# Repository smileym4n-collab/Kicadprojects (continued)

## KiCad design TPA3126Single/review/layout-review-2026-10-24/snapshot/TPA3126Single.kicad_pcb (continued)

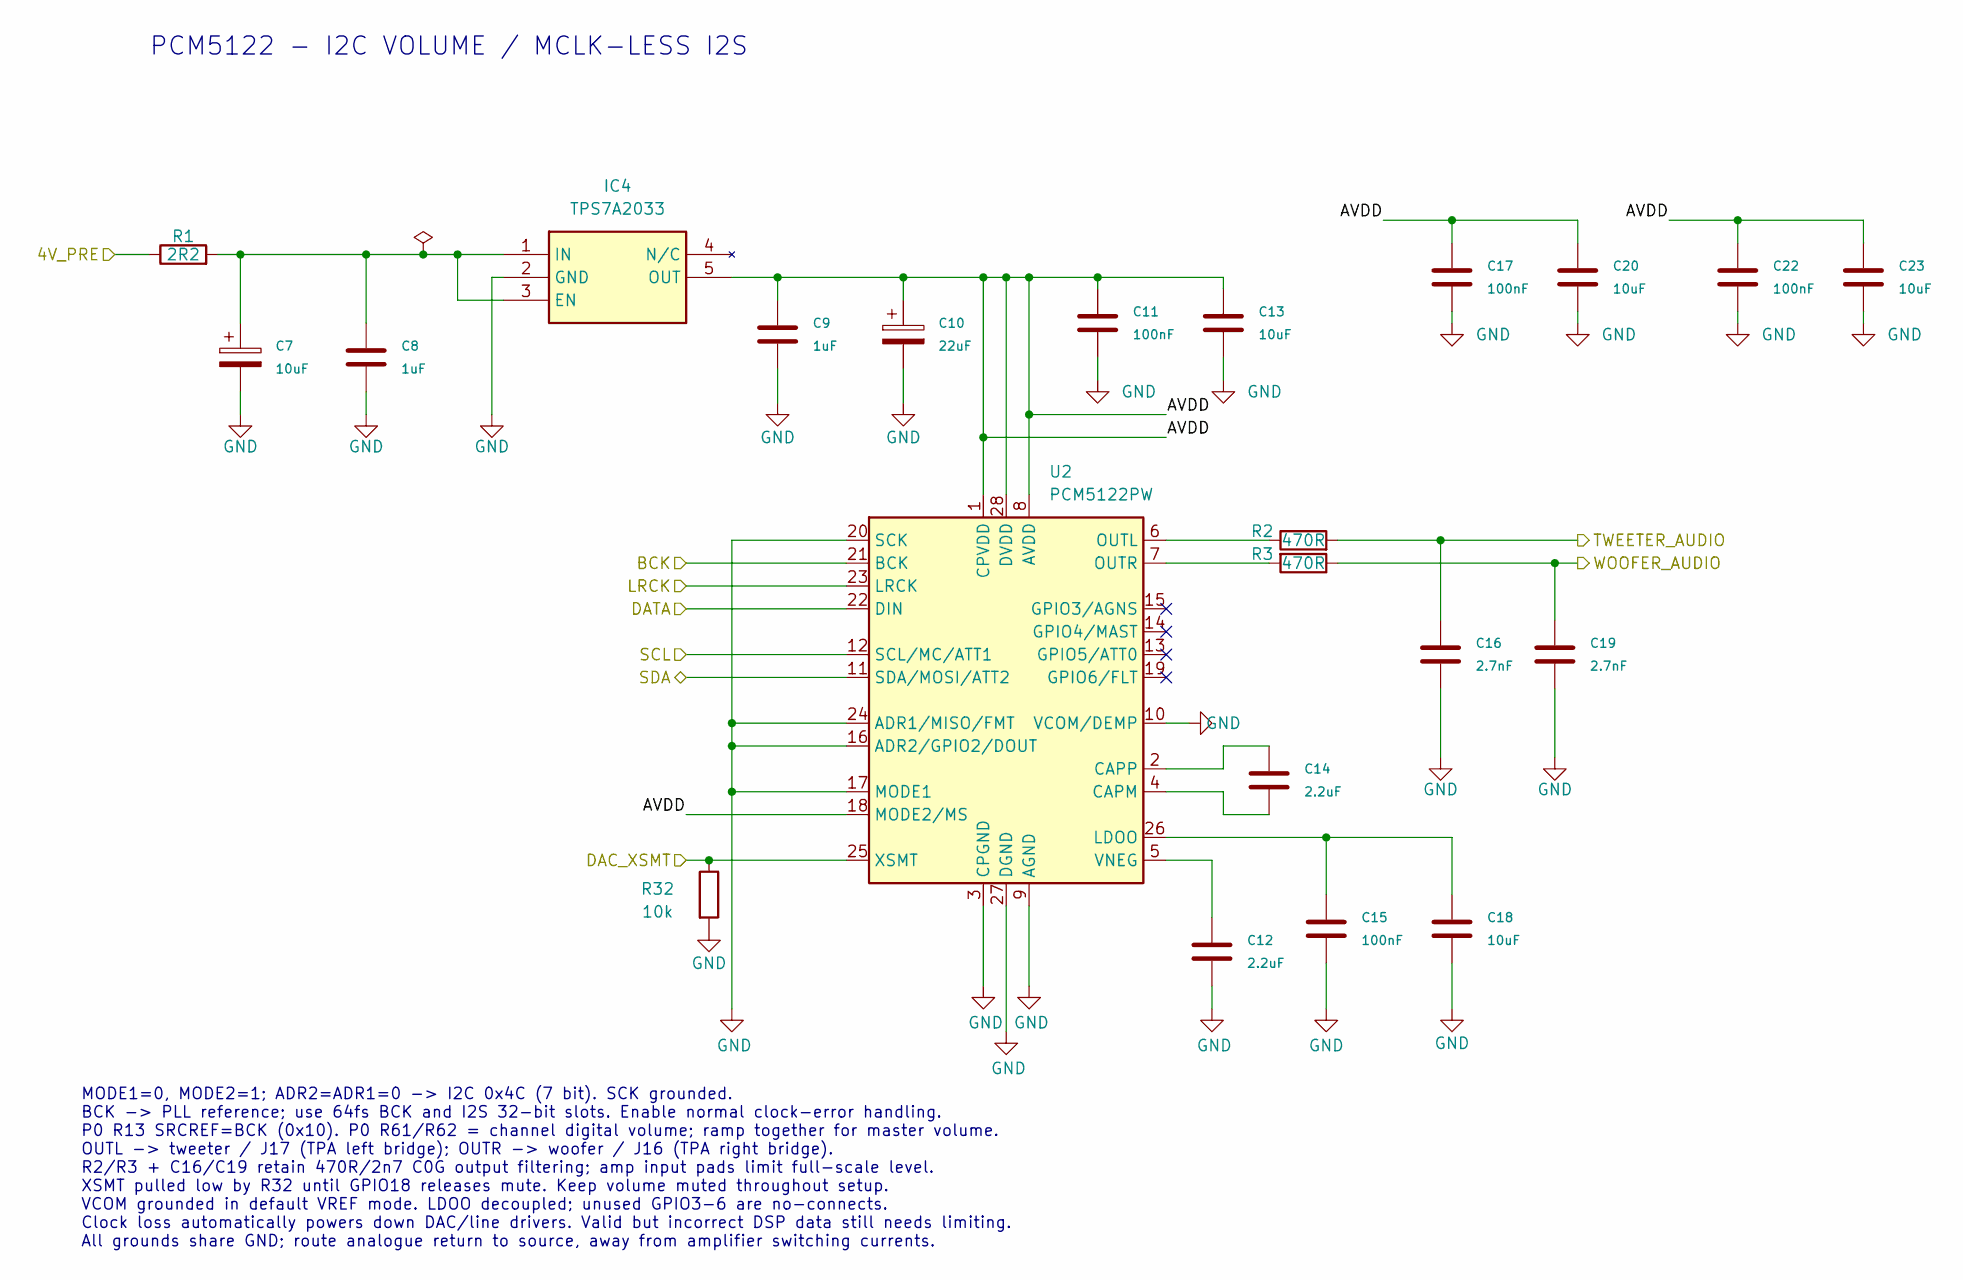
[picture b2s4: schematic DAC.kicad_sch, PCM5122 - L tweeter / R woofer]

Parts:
C7: 10uF; CP_Radial_D5.0mm_P2.00mm; MPN UFW1H100MDD
C8, C9: 1uF; C_1206_3216Metric_Pad1.33x1.80mm_HandSolder; MPN CL31B105KBHNFNE
C10: 22uF; CP_Radial_D5.0mm_P2.00mm; MPN UFW1E220MDD
C11, C15, C17, C22: 100nF; C_1206_3216Metric_Pad1.33x1.80mm_HandSolder; MPN C1206C104K5RACTU
C12, C14: 2.2uF; C_0805_2012Metric_Pad1.18x1.45mm_HandSolder; MPN CL21B225KPFNNNE
C13, C20, C23: 10uF; C_0805_2012Metric_Pad1.18x1.45mm_HandSolder; MPN CL21A106KOQNNNF
C16, C19: 2.7nF; C_0805_2012Metric_Pad1.18x1.45mm_HandSolder; MPN 0805N272J500CT
C18: 10uF; C_1206_3216Metric_Pad1.33x1.80mm_HandSolder; MPN TMK316B7106KL-TD
IC4: TPS7A2033; SOT95P280X145-5N; Mouser Part Number 595-TPS7A2033PDBVR
R1: 2R2; R_0805_2012Metric_Pad1.20x1.40mm_HandSolder
R2, R3: 470R; R_0805_2012Metric_Pad1.20x1.40mm_HandSolder
R32: 10k; R_0603_1608Metric_Pad0.98x0.95mm_HandSolder; Manufacturer_Part_Number RC0603FR-0710KL
U2: PCM5122PW; TSSOP-28_4.4x9.7mm_P0.65mm; MPN PCM5122PWR

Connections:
/4V_PRE: R1.1; also elsewhere on the board
/AMP/TWEETER_AUDIO: C16.1, R2.2; also elsewhere on the board
/AMP/WOOFER_AUDIO: C19.1, R3.1; also elsewhere on the board
/DAC/AVDD: C9.1, C10.1, C11.1, C13.1, C17.1, C20.1, C22.1, C23.1, IC4.5 (OUT), U2.1 (CPVDD), U2.8 (AVDD), U2.18 (MODE2/MS), U2.28 (DVDD)
/DAC/BCK: U2.21 (BCK); also elsewhere on the board
/DAC/DAC_XSMT: R32.1, U2.25 (XSMT); also elsewhere on the board
/DAC/DATA: U2.22 (DIN); also elsewhere on the board
/DAC/LRCK: U2.23 (LRCK); also elsewhere on the board
/ESP32/SCL: U2.12 (SCL/MC/ATT1); also elsewhere on the board
/ESP32/SDA: U2.11 (SDA/MOSI/ATT2); also elsewhere on the board
GND: C7.2, C8.2, C9.2, C10.2, C11.2, C12.2, C13.2, C15.2, C16.2, C17.2, C18.2, C19.2, C20.2, C22.2, C23.2, IC4.2 (GND), R32.2, U2.3 (CPGND), U2.9 (AGND), U2.10 (VCOM/DEMP), U2.16 (ADR2/GPIO2/DOUT), U2.17 (MODE1), U2.20 (SCK), U2.24 (ADR1/MISO/FMT), U2.27 (DGND); also elsewhere on the board
unnamed: C7.1, C8.1, IC4.1 (IN), IC4.3 (EN), R1.2
unnamed: C14.2, U2.4 (CAPM)
unnamed: C14.1, U2.2 (CAPP)
unnamed: C15.1, C18.1, U2.26 (LDOO)
unnamed: R2.1, U2.6 (OUTL)
unnamed: R3.2, U2.7 (OUTR)
unnamed: C12.1, U2.5 (VNEG)

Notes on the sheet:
MODE1=0, MODE2=1; ADR2=ADR1=0 -> I2C 0x4C (7 bit). SCK grounded. BCK -> PLL reference; use 64fs BCK and I2S 32-bit slots. Enable normal clock-error handling. P0 R13 SRCREF=BCK (0x10). P0 R61/R62 = channel digital volume; ramp together for master volume. OUTL -> tweeter / J17 (TPA left bridge); OUTR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
PCM5122 - I2C VOLUME / MCLK-LESS I2S

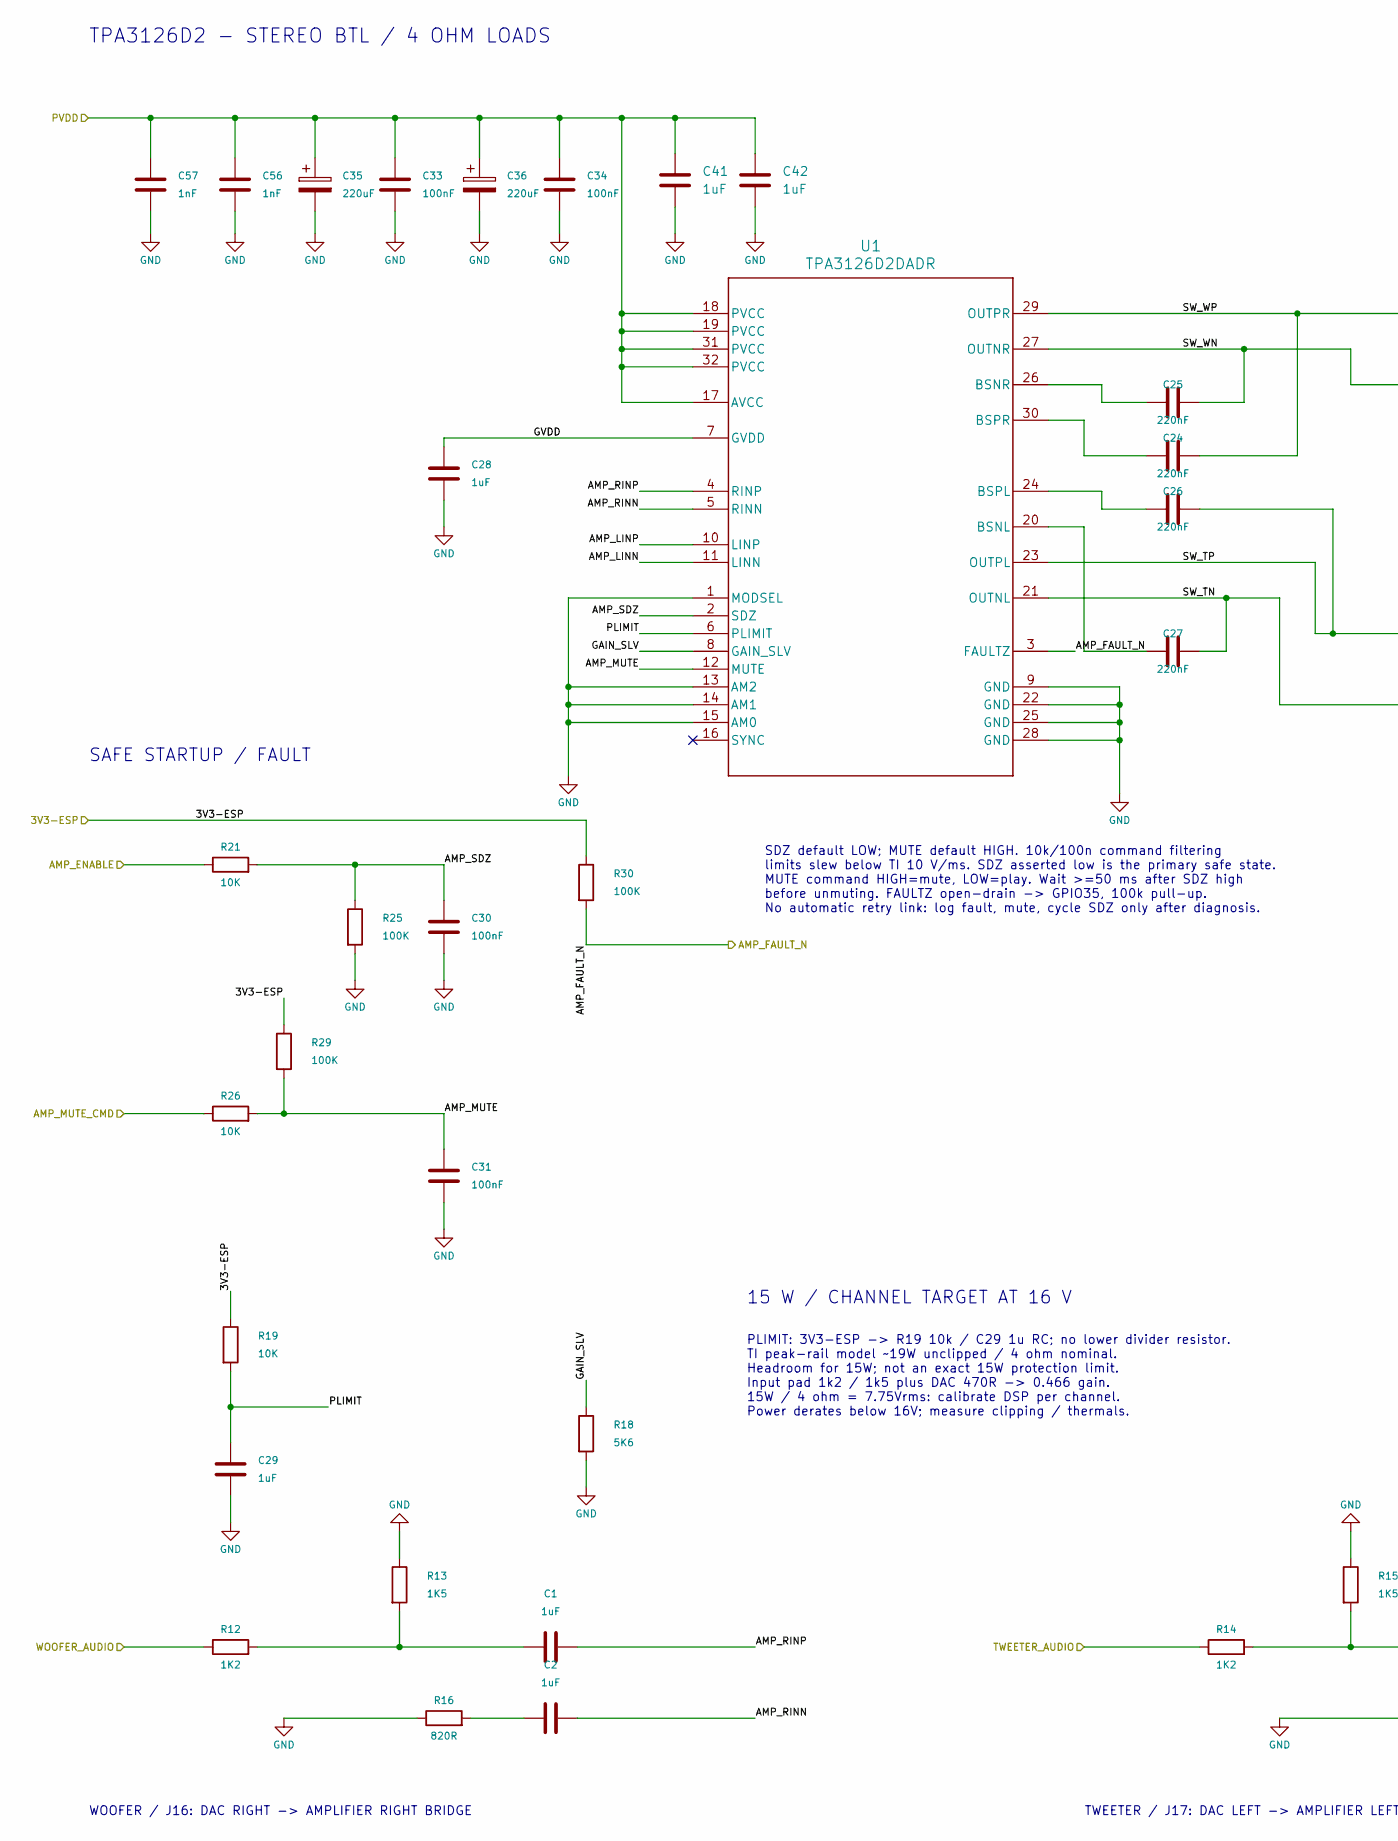
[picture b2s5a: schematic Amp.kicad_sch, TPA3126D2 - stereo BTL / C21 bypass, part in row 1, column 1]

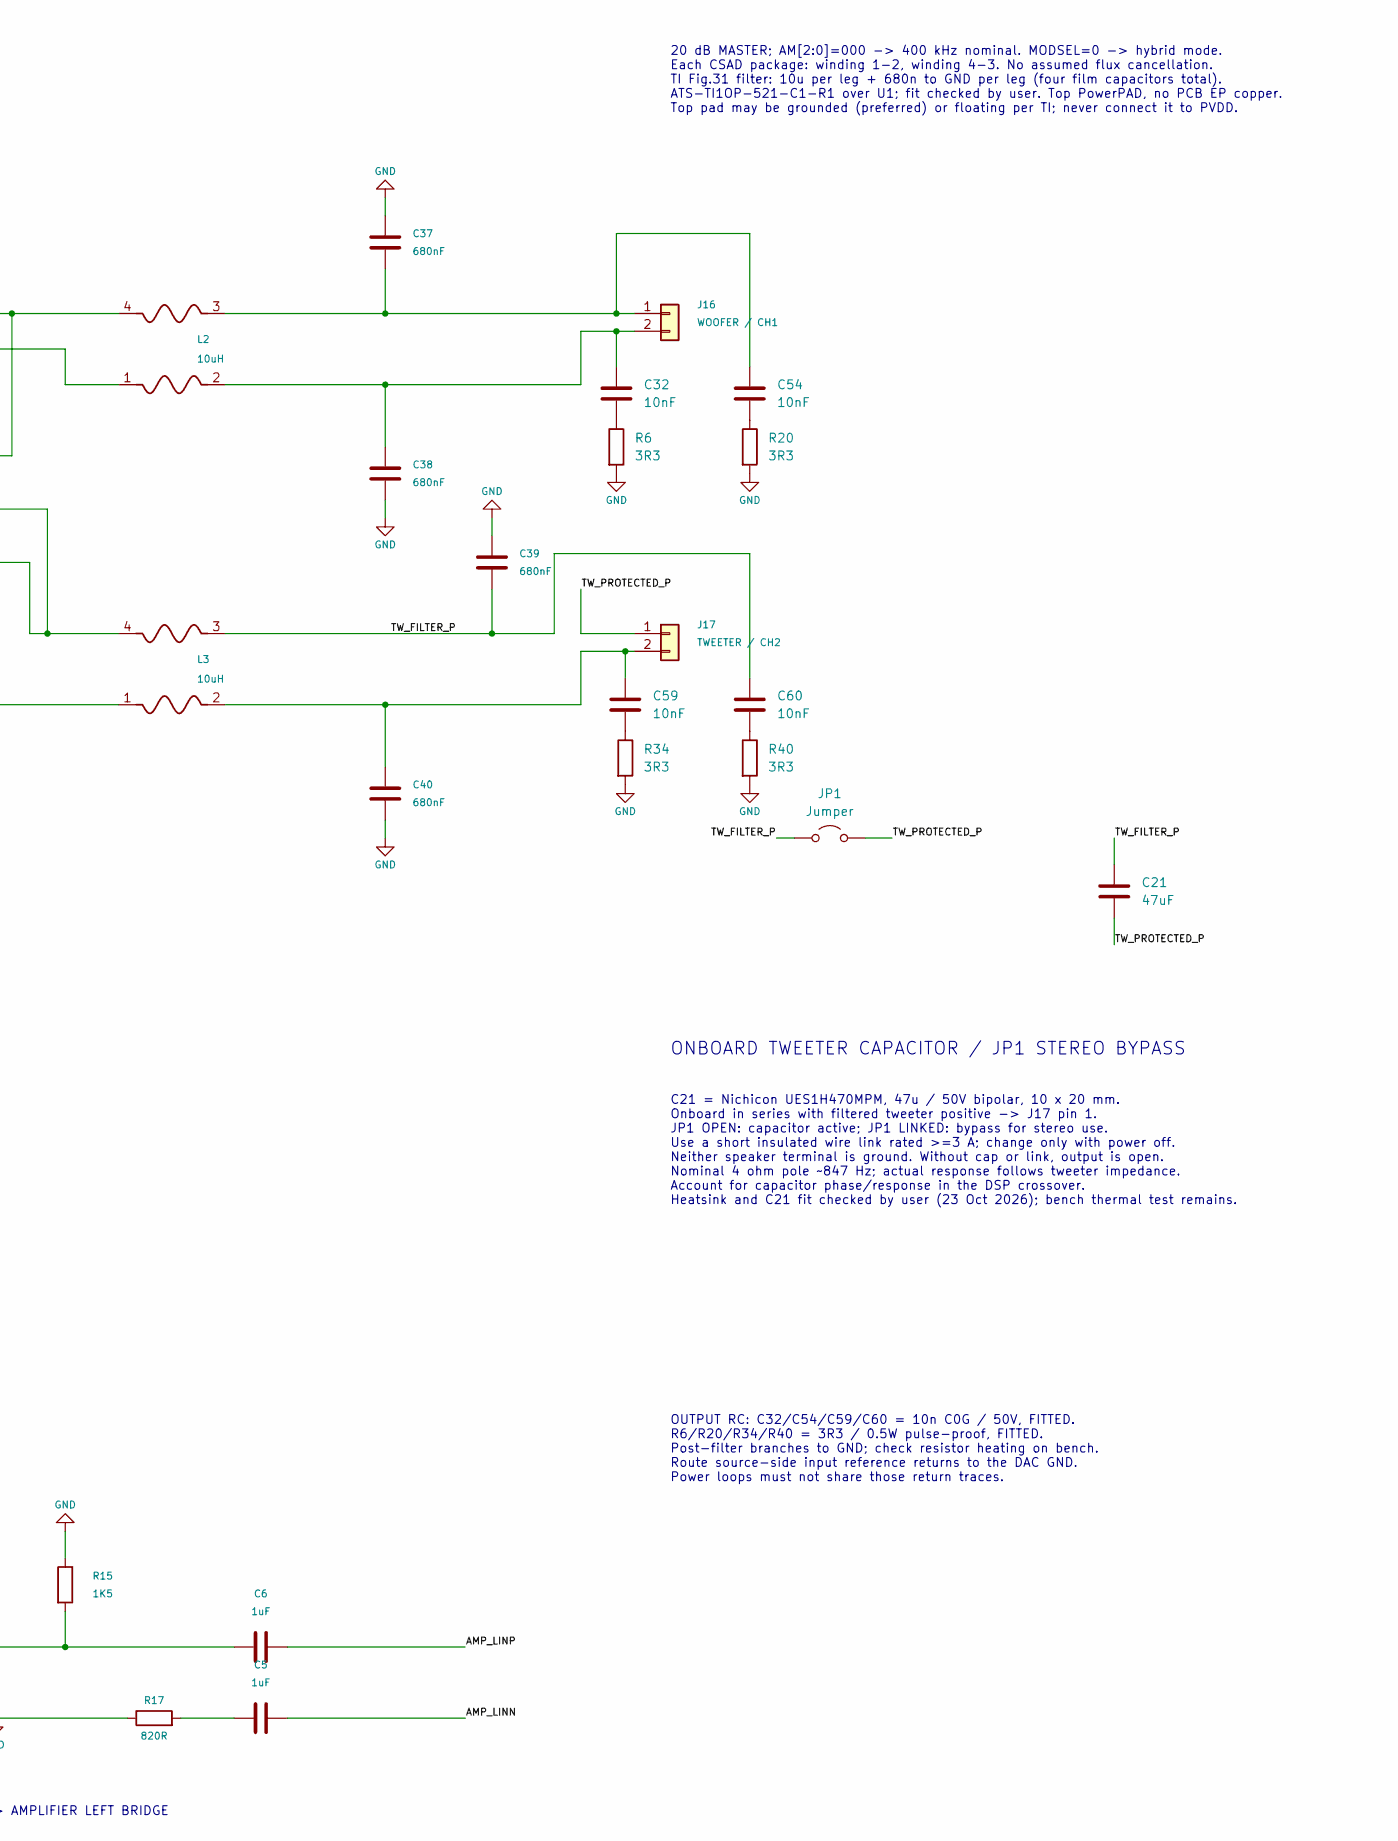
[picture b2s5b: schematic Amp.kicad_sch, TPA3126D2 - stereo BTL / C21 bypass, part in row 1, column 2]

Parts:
C1, C2, C5, C6: 1uF; C_Rect_L7.2mm_W5.0mm_P5.00mm; Voltage_Rating 63 V; Tolerance 5%; MPN R82DC4100AA60J
C21: 47uF; C_Radial_D10.0mm_H20.0mm_P5.00mm; Voltage_Rating 50 V; Tolerance 20%; MPN UES1H470MPM
C24, C25, C26, C27: 220nF; C_0805_2012Metric_Pad1.18x1.45mm_HandSolder; MPN CL21B224KAFNNNE
C28: 1uF; C_0805_2012Metric_Pad1.18x1.45mm_HandSolder; Voltage_Rating 25 V; Tolerance 10%; MPN C0805C105K3RACTU
C29: 1uF; C_1206_3216Metric_Pad1.33x1.80mm_HandSolder; MPN CL31B105KBHNFNE
C30, C31, C33, C34: 100nF; C_0603_1608Metric_Pad1.08x0.95mm_HandSolder; Voltage_Rating 50 V; Tolerance 10%; MPN MC0603B104K500CT
C32, C54, C59, C60: 10nF; C_0805_2012Metric_Pad1.18x1.45mm_HandSolder; Voltage_Rating 50 V; Tolerance 1%; MPN MC0805N103F500CT
C35, C36: 220uF; CP_Radial_D8.0mm_P3.50mm; MPN 35ZLH220MEFC8X11.5
C37, C38, C39, C40: 680nF; C_Rect_L18.0mm_W7.0mm_P15.00mm_FKS3_FKP3; MPN ECW-FE2W684J
C41, C42: 1uF; C_1206_3216Metric_Pad1.33x1.80mm_HandSolder
C56, C57: 1nF; C_0603_1608Metric_Pad1.08x0.95mm_HandSolder; Voltage_Rating 50 V; Tolerance 10%; MPN CL10B102KB8NNNC
J16: WOOFER / CH1; Molex_KK-396_5273-02A_1x02_P3.96mm_Vertical; MPN 09-65-2028
J17: TWEETER / CH2; Molex_KK-396_5273-02A_1x02_P3.96mm_Vertical; MPN 09-65-2028
JP1: Jumper; TestPoint_2Pads_Pitch5.08mm_Drill1.3mm
L2, L3: 10uH; CSAD0660-100M; MPN CSAD0660-100M
R6, R20, R34, R40: 3R3; R_0805_2012Metric_Pad1.20x1.40mm_HandSolder; Tolerance 1%; MPN CRCW08053R30FKEAHP
R12, R14: 1K2; R_0805_2012Metric_Pad1.20x1.40mm_HandSolder; MPN RMCF0805FT1K20
R13, R15: 1K5; R_0805_2012Metric_Pad1.20x1.40mm_HandSolder; MPN RMCF0805FT1K50
R16, R17: 820R; R_0805_2012Metric_Pad1.20x1.40mm_HandSolder
R18: 5K6; R_0805_2012Metric_Pad1.20x1.40mm_HandSolder; MPN RMCF0805FT5K60
R19, R21, R26: 10K; R_0805_2012Metric_Pad1.20x1.40mm_HandSolder; MPN RK73B2ATTD103J
R25, R29, R30: 100K; R_0805_2012Metric_Pad1.20x1.40mm_HandSolder
U1: TPA3126D2DADR; Texas_DAD0032A_HTSSOP-32_6.1x11mm_P0.65mm_TopEP3.71x3.81mm; MPN TPA3126D2DADR

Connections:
/3V3-ESP: R19.1, R29.1, R30.1; also elsewhere on the board
/AMP/AMP_ENABLE: R21.1; also elsewhere on the board
/AMP/AMP_FAULT_N: R30.2, U1.3 (FAULTZ); also elsewhere on the board
/AMP/AMP_LINN: C5.2, U1.11 (LINN)
/AMP/AMP_LINP: C6.2, U1.10 (LINP)
/AMP/AMP_MUTE: C31.1, R26.2, R29.2, U1.12 (MUTE)
/AMP/AMP_MUTE_CMD: R26.1; also elsewhere on the board
/AMP/AMP_RINN: C2.2, U1.5 (RINN)
/AMP/AMP_RINP: C1.2, U1.4 (RINP)
/AMP/AMP_SDZ: C30.1, R21.2, R25.1, U1.2 (SDZ)
/AMP/GAIN_SLV: R18.1, U1.8 (GAIN_SLV)
/AMP/GVDD: C28.1, U1.7 (GVDD)
/AMP/PLIMIT: C29.1, R19.2, U1.6 (PLIMIT)
/AMP/SW_TN: C27.2, L3.1, U1.21 (OUTNL)
/AMP/SW_TP: C26.2, L3.4, U1.23 (OUTPL)
/AMP/SW_WN: C25.2, L2.1, U1.27 (OUTNR)
/AMP/SW_WP: C24.2, L2.4, U1.29 (OUTPR)
/AMP/TWEETER_AUDIO: R14.1; also elsewhere on the board
/AMP/TW_FILTER_P: C21.1, C39.2, C60.1, JP1.1 (A), L3.3
/AMP/TW_PROTECTED_P: C21.2, J17.1, JP1.2 (B)
/AMP/WOOFER_AUDIO: R12.1; also elsewhere on the board
/PVDD: C33.1, C34.1, C35.1, C36.1, C41.1, C42.1, C56.1, C57.1, U1.17 (AVCC), U1.18 (PVCC), U1.19 (PVCC), U1.31 (PVCC), U1.32 (PVCC); also elsewhere on the board
GND: C28.2, C29.2, C30.2, C31.2, C33.2, C34.2, C35.2, C36.2, C37.1, C38.2, C39.1, C40.2, C41.2, C42.2, C56.2, C57.2, R6.2, R13.1, R15.1, R16.1, R17.1, R18.2, R20.2, R25.2, R34.2, R40.2, U1.1 (MODSEL), U1.9 (GND), U1.13 (AM2), U1.14 (AM1), U1.15 (AM0), U1.22 (GND), U1.25 (GND), U1.28 (GND); also elsewhere on the board
unnamed: C1.1, R12.2, R13.2
unnamed: C2.1, R16.2
unnamed: C5.1, R17.2
unnamed: C6.1, R14.2, R15.2
unnamed: C32.2, R6.1
unnamed: C54.2, R20.1
unnamed: C59.2, R34.1
unnamed: C60.2, R40.1
unnamed: C37.2, C54.1, J16.1, L2.3
unnamed: C32.1, C38.1, J16.2, L2.2
unnamed: C40.1, C59.1, J17.2, L3.2
unnamed: C27.1, U1.20 (BSNL)
unnamed: C25.1, U1.26 (BSNR)
unnamed: C26.1, U1.24 (BSPL)
unnamed: C24.1, U1.30 (BSPR)

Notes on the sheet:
C21 = Nichicon UES1H470MPM, 47u / 50V bipolar, 10 x 20 mm. Onboard in series with filtered tweeter positive -> J17 pin 1. JP1 OPEN: capacitor active; JP1 LINKED: bypass for stereo use. Use a short insulated wire link rated >=3 A; change only with power off. Neither speaker terminal is ground. Witho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
ONBOARD TWEETER CAPACITOR / JP1 STEREO BYPASS
SAFE STARTUP / FAULT
WOOFER / J16: DAC RIGHT -> AMPLIFIER RIGHT BRIDGE
OUTPUT RC: C32/C54/C59/C60 = 10n C0G / 50V, FITTED. R6/R20/R34/R40 = 3R3 / 0.5W pulse-proof, FITTED. Post-filter branches to GND; check resistor heating on bench. Route source-side input reference returns to the DAC GND. Power loops must not share those return traces.
SDZ default LOW; MUTE default HIGH. 10k/100n command filtering limits slew below TI 10 V/ms. SDZ asserted low is the primary safe state. MUTE command HIGH=mute, LOW=play. Wait >=50 ms after SDZ high before unmuting. FAULTZ open-drain -> GPIO35, 100k pull-up. No automatic retry link: log fault, mute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
TPA3126D2 - STEREO BTL / 4 OHM LOADS
15 W / CHANNEL TARGET AT 16 V
TWEETER / J17: DAC LEFT -> AMPLIFIER LEFT BRIDGE
20 dB MASTER; AM[2:0]=000 -> 400 kHz nominal. MODSEL=0 -> hybrid mode. Each CSAD package: winding 1-2, winding 4-3. No assumed flux cancellation. TI Fig.31 filter: 10u per leg + 680n to GND per leg (four film capacitors total). ATS-TI1OP-521-C1-R1 over U1; fit checked by user. Top PowerPAD, no PCB 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
PLIMIT: 3V3-ESP -> R19 10k / C29 1u RC; no lower divider resistor. TI peak-rail model ~19W unclipped / 4 ohm nominal. Headroom for 15W; not an exact 15W protection limit. Input pad 1k2 / 1k5 plus DAC 470R -> 0.466 gain. 15W / 4 ohm = 7.75Vrms: calibrate DSP per channel. Power derates below 16V; mea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

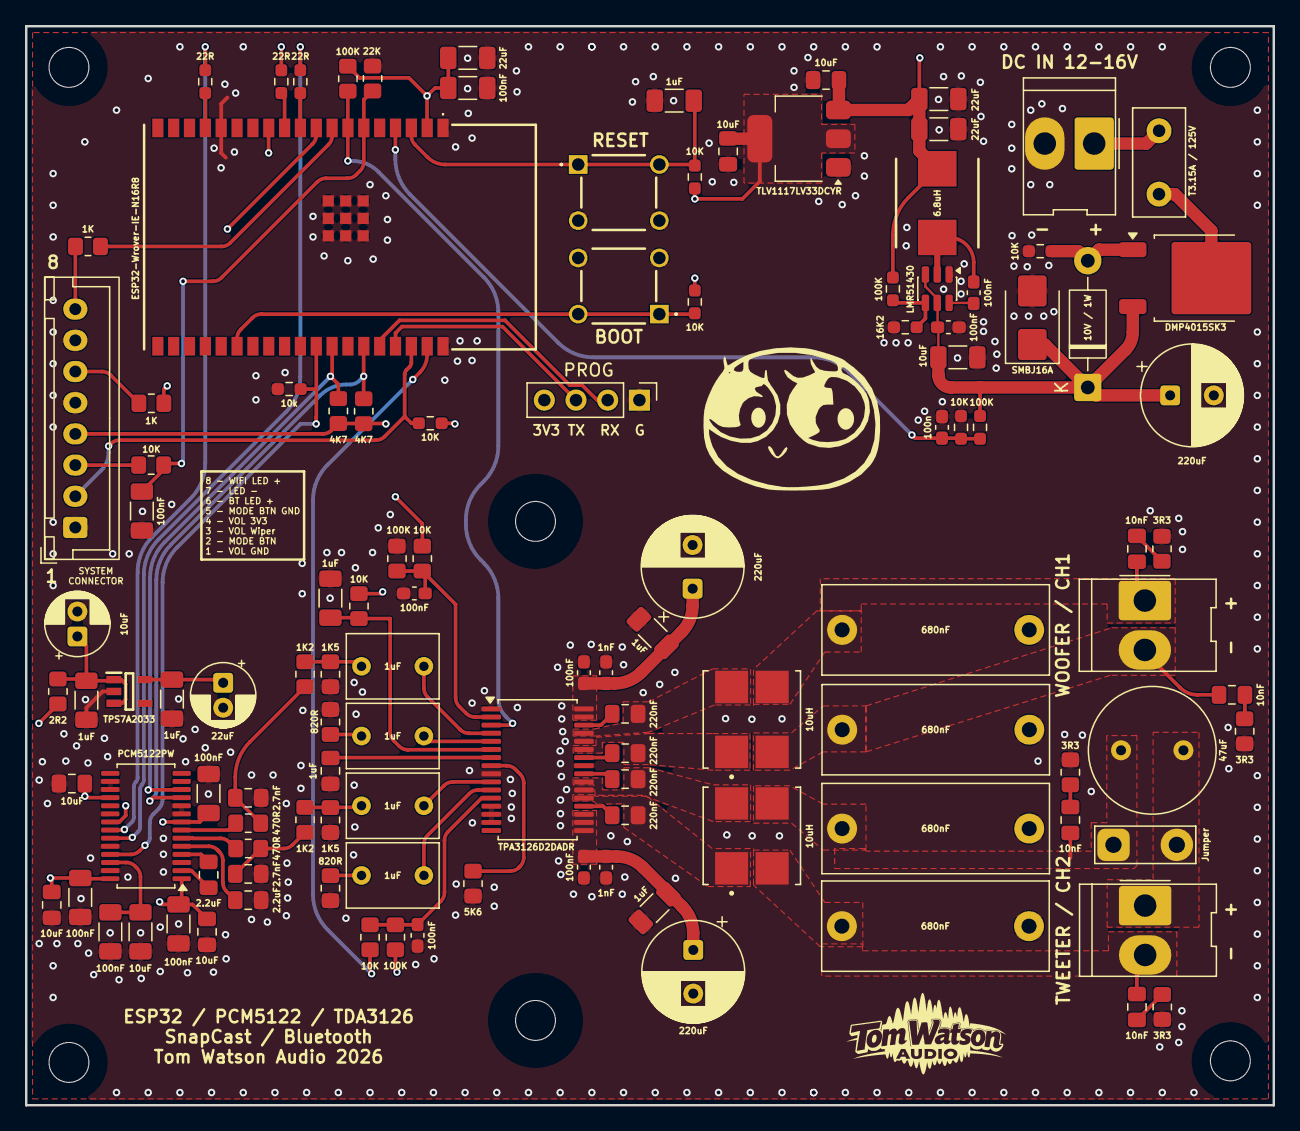
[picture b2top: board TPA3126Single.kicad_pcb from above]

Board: 4 copper layers, 100.0 x 86.5 mm, 122 parts (0 on the bottom side), 74 nets.
